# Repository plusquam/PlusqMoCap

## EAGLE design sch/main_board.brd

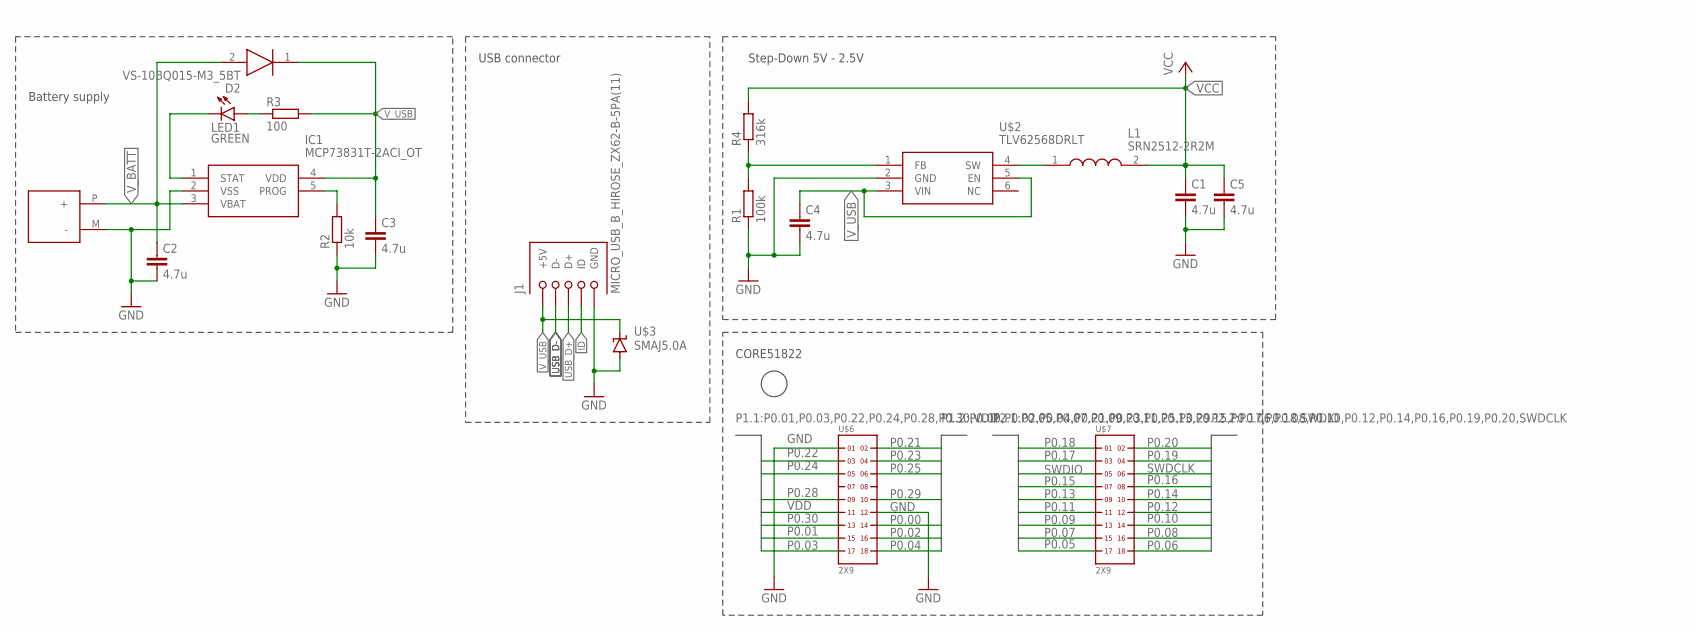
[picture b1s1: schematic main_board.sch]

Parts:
C1, C2, C3, C4, C5: 4.7u; C1206
D2: VS-10BQ015-M3_5BT; DIOM5436X244N
IC1: MCP73831T-2ACI_OT; SOT95P270X145-5N
J1: MICRO_USB_B_HIROSE_ZX62-B-5PA(11); USB_MICRO_B-HIROSE-ZX62-B-5PA(11)
L1: SRN2512-2R2M; INDPM2622X120N
LED1: GREEN; CHIPLED_1206
R1: 100k; R1206
R2: 10k; R1206
R3: 100; R1206
R4: 316k; R1206
U$1: BAT_FLAT_PAD; BATTERY_FLAT_PAD
U$2: TLV62568DRLT; SOT563
U$3: SMAJ5.0A; DO-214AC
U$6, U$7: 2X9

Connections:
GND: C1.2, C2.2, C3.2, C4.2, C5.2, IC1.2 (VSS), J1.5 (GND), R1.1, R2.1, U$1.M (-), U$2.2 (GND), U$3.A, U$6.1, U$6.12
ID: J1.4 (ID)
unnamed: LED1.A, R3.1
unnamed: IC1.1 (STAT), LED1.C
unnamed: IC1.5 (PROG), R2.2
unnamed: L1.1, U$2.4 (SW)
unnamed: R1.2, R4.1, U$2.1 (FB)
P0.00: U$6.14
P0.01: U$6.15
P0.02: U$6.16
P0.03: U$6.17
P0.04: U$6.18
P0.05: U$7.17
P0.06: U$7.18
P0.07: U$7.15
P0.08: U$7.16
P0.09: U$7.13
P0.10: U$7.14
P0.11: U$7.11
P0.12: U$7.12
P0.13: U$7.9
P0.14: U$7.10
P0.15: U$7.7
P0.16: U$7.8
P0.17: U$7.3
P0.18: U$7.1
P0.19: U$7.4
P0.20: U$7.2
P0.21: U$6.2
P0.22: U$6.3
P0.23: U$6.4
P0.24: U$6.5
P0.25: U$6.6
P0.28: U$6.9
P0.29: U$6.10
P0.30: U$6.13
SWDCLK: U$7.6
SWDIO: U$7.5
USB_D+: J1.3 (D+)
USB_D-: J1.2 (D-)
VCC: C1.1, C5.1, L1.2, R4.2
VDD: U$6.11
V_BATT: C2.1, D2.2 (A), IC1.3 (VBAT), U$1.P (+)
V_USB: C3.1, C4.1, D2.1 (K), IC1.4 (VDD), J1.1 (+5V), R3.2, U$2.3 (VIN), U$2.5 (EN), U$3.C

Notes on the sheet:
Step-Down 5V - 2.5V
USB connector
Battery supply
CORE51822

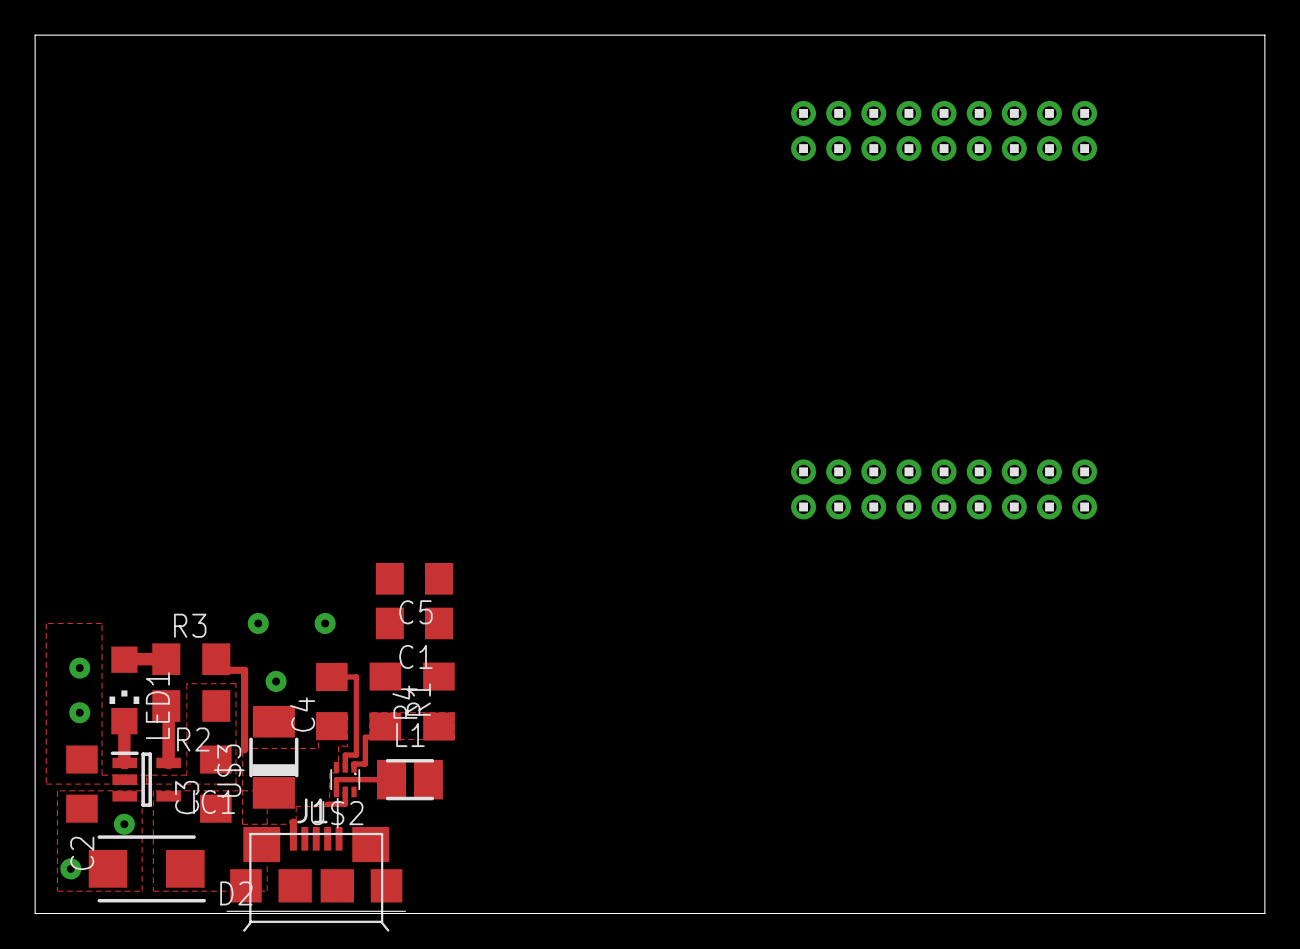
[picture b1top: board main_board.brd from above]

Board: 2 copper layers, 70.0 x 50.0 mm, 19 parts (1 on the bottom side), 9 nets.

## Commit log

2019-04-07 Initial commit.
2019-04-07 Define structure of the repository.
2019-04-29 - Add power supply for main board,
2019-05-06 Add MPU9250 docs, reorganize doc directory
2019-05-06 Add MPU design block
2019-05-17 Create LICENSE
2019-05-17 Move all project files to PlusqMoCap_HW submodule.
2019-05-17 Add HW and SW submodules.
2019-08-03 Remove LICENSE file.
2019-08-03 Update SW submodule
2019-08-03 Add Dongle submodule
2019-09-13 Add ROS submodule
2019-09-13 SW submodule update
2019-09-13 Readd Dongle submodule
2019-09-13 Update of the rest of submodules. Final version for master's degree
2019-09-26 Update HW repo
